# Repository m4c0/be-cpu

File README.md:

# be-cpu

Before trying to dig in this project, please check out Ben Eater's [YouTube Playlist](https://www.youtube.com/watch?v=HyznrdDSSGM&list=PLowKtXNTBypGqImE405J2565dvjafglHU) first. That's an amazing material, and he deserves a lot of credits (and tips, as well).

This repository contains my own version of Ben Eater's CPU. Some people build cars in their spare time, I build a CPU. I'm open-sourcing it because Ben's design is open as well - and Open Source Hardware is a cool concept. Maybe there'll be some videos on my own in the future; maybe I'll sell kits... Only time will tell.

## Mission

Be fun. "Fun" is more important than "cool". The final result may be cool, but the path will definitely be fun. It's what [Arduino](https://www.arduino.cc) does in the microcontroller market - there are ICs faster than ATmega, with more memory, IOs and resources in general, but it's fun to work with Arduino and you can make cool stuff with it. 

## General design decisions

One noticeable difference from Ben's original design is the usage of SMD instead of THT. Mainly because I like designing and soldering using SMD (althought I'm still learning).

Also, due to pricing and availability, the 74LS chips are being replaced with their CMOS variants - mostly 74HC. It has a wide range of voltages, supporting from 2V up to 6V. 74HCT would be strictier, supporting 4.5 to 5V, which is right at the edge of what USB can provide. The 2-6V range allows us to change the supply voltage as required.

Ben also tried to split his design into modules, but not all modules had its own breadbord. The same goes here, but the design is strongly modular, with one module per "PCB card".

The clock is slow - this is not a design to run in the scale of MHz. It's meant to see what the CPU is doing as it runs simple algorithms, in a very low clock (less than 1kHz - TBC). This also allows the design to be "EMI-free" (as in "don't need to care about EMI"). 2-layer boards and lack of extra ground pins will be a thing here.

Note: being able to implement [RISC-V](https://riscv.org) would be interesting, but definitely unfeasible with those modules.

## Versions

*Note:* Due to time (and money) restrictions, some combination of version/modules may not be tested, yet.

### BE - Eater's version

This is as close as possible to Ben's own version. There's no substantial change in his design, other than changes that are required to make the CPU work, and current-limiting resistors.

Since Ben's design works, troubleshooting those modules will be easier. This version then acts as a "reference design" when experimenting new designs and ideas for other versions.

#### Clock

The version 0.1 follows these original design decisions (shown in [this video](https://www.youtube.com/watch?v=SmQ5K7UQPMM)):

* One astable 555 as a clock
* One monostable 555 as a push button debouncer
* One bistable 555 as a switch debouncer
* One 7404, one 7408 and one 7432 to apply the logic to get the result of the three 555s as a final clock
* One LED with the clock output
* The button and the switch to be debounced
* A trimpot to select the astable clock speed

I took the liberty of doing these changes:

* Add three pads with the outputs of the 555s. This way, we can see the results of the individual ICs with a voltimeter/oscilloscope or by soldering LEDs. This gives the same visual feedback as used by Ben until he finishes the module
* The final board has male pin headers for VCC/GND, CLK/HLT, and eight extras, to reserve space for the bus. This is an attempt to make a standard for the modules, in a way both bus and signals are handled by a transversal companion board (to be developed).
* Pins for the 74xx family were changed to allow a more compact design

The whole design currently fits in a 4x3.4cm board. You can buy one for yourself at [OSHPark](https://oshpark.com/shared_projects/r4cIYBAv).

Improvements for the next revision:

* Add a OSH stamp to the back silk
* Increase the LED resistor (currently at 220), because the LED is annoyingly bright now. It seems 470 gives a nice result, but testing showed it varies with the load at the CLK pin - powering another LED from CLK drastically reduces the onboard LED brightness. This may be the end result after all modules are tied up to the same CLK bus.
* Increase the push button debounce time (it works, but it feels faster than it should)
* Find more SMD-friendly button, switch and trimpot
* Flip the design. The pin header is on top, so all text is upside-down and it drives me nuts

#### Register

The version 0.1 of that module contain these from the original design (shown in [this video](https://www.youtube.com/watch?v=CiMaWbz_6E8)):

* Two 74173 (quad D-Flip Flop with tri-state output, async clear and chip-select) to read from the bus and store the value
* One 74245 (tri-state bi-directional buffer) to enable output the value to the bus on-demand
* Eight LEDs to show the output of the 74173 (effectively, the value of the register, even if not outputting to the bus)
* There are four signals: clock, reset (tied up to the MR of the 74173), output enabled (inverted), input enabled (inverted)

There's only one considerable change in this design. The output LEDs has current limiting resistors - currently 220ohms.

It also contains an extra 8-bit header from the output of the 74173. This serves for "hot linking" the register without the bus - in this case, "A" and "B" registers and the ALU input.

The whole design currently fits in a 4.5x3.2cm board. You can buy one for yourself at [OSHPark](https://oshpark.com/shared_projects/CUKuVAHy).

Improvements for the next revision:

* Add a OSH stamp to the back silk
* Consider a dual hot-link pin header, allowing to "sandwich" the ALU using standard headers
* Realign the hot-link to be easier to copy over to the ALU

#### ALU

The version 0.1 of that module contain these from the original design (shown in [Ben's site](https://eater.net/8bit/alu)):

* Two 74283 (4-bit ALU)
* Two 7486 (Quad-XOR) to conditionally invert input "B"
* One 74245 (tri-state bi-directional buffer) to enable output the value to the bus on-demand
* Eight LEDs to show the output of the 74283 (effectively, the output of the ALU, even if not outputting to the bus)
* One 7402 (Quad-NOR) and one 7408 (Quad-AND) to create the "zero flag" whenever the output of ALU is zero
* One 74173 (Quad D-FF) to act as a "flag register", storing the "zero flag" and the "carry flag"
* Two extra LEDs to show ZF and CF (unbuffered)

This board exposes a double-sided 16-bit header (8-bit each side) to hot-link A and B registers.

The whole design currently fits in a 5.7x3.8cm board.

#### RAM

Currently on research. Until said otherwise, this module won't have a "BE" version, since there's no 74189 in SMD. All major manufacturers discontinued that product, and the "unbranded" Chinese manufacturers only sells them in THT.

#### Bus

No board yet, only some ideas. This should contain pin headers for all modules. All signals will be hardcoded, to simplify the design of the individual modules.

### BM - My own version

This is my own version of Ben's CPU. It will replace components and change architecture. Since it's laxed, more experimental features goes here.

#### Clock

Still in planning. Current plan:

* One astable 555 as a clock
* A RC+Shimitt Trigger for debouncing the push button

Questions to answer:

* Is there a better way to debounce the toggle switch?
* What's the minimal circuit to do the logic (switch+halt)?

#### Register

Questions/ideas:

* Use a 74377 (Octal DFF), saving one IC
* Check if the 74377 can drive eight LEDs - maybe use a ULN2803 as LED driver
* Remove the reset input. A "global reset" may be achieveable if we keep the pull-down resistors on the bus and we enable all register's input - this way, the bus will be zeroed and the registers will latch that value.
* Can we send IE/OE already in sync with the clock?

#### ALU

#### RAM

#### Bus

Idea:

* Allow customization of the bus signal

### BC - Compact and cheap

This is will be smaller and containing less modules (or cheaper ones). All modules will be non-suitable for children under 4, because they will be tiny (1.35"/3.7cm wide). It provides building blocks to easily test high level architectures, while still being a good educational toy.

The main bus will probably be done with card edges connecting to a `HSEC8-120-01-SM-DV-A` from Samtec (or, at least, some 0.8mm similar product).

The connector will be partially reversible. When reversed, it will allow the board to operate on a different bus. One side will be the "main bus" and the other will be the "secondary bus".

#### Register

This is a 17.2x35mm board with a 74377 (Octal DFF), a 74245 (Bus Driver) and a ULN2803 (LED Driver). It supports a single bus, like Ben's original design. Also following his design, register "A" will be on main bus, and "B" will be secondary. Probably...

The absence of reset follows the same idea used in BM - the reset can be done by enabling the output and leaving the bus grounded.

Currently, this is not tested yet. The BM will be used as "test bench" for some ideas, like removing the ULN2803 or changing the flip-flop IC.

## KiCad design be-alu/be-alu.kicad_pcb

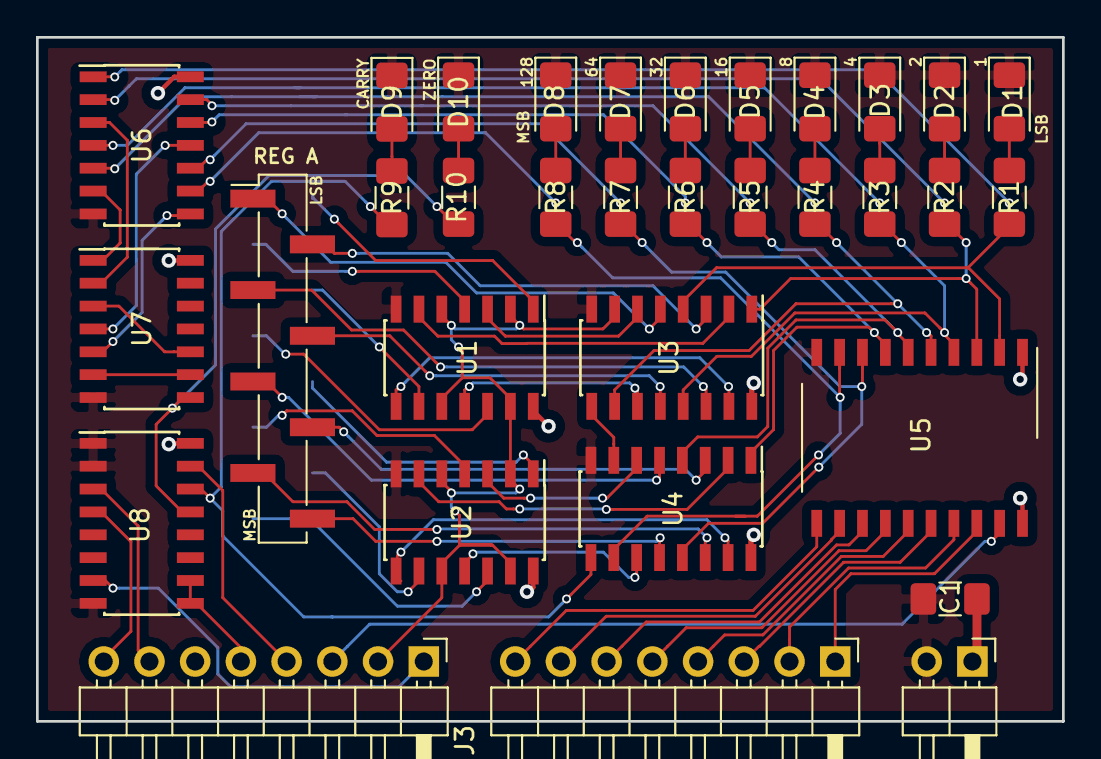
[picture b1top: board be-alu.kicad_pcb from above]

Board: 2 copper layers, 57.0 x 38.0 mm, 34 parts (1 on the bottom side), 68 nets.

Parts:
C1: 0.1u; C_1206_3216Metric_Pad1.42x1.75mm_HandSolder
D1, D2, D3, D4, D5, D6, D7, D8, D9, D10: LED; LED_1206_3216Metric_Pad1.42x1.75mm_HandSolder
J1: Conn_01x02; PinHeader_1x02_P2.54mm_Horizontal
J2, J3: Conn_01x08; PinHeader_1x08_P2.54mm_Horizontal
J4, J5: Conn_01x08; PinHeader_1x08_P2.54mm_Vertical_SMD_Pin1Left
R1, R2, R3, R4, R5, R6, R7, R8, R9, R10: 220; R_1206_3216Metric_Pad1.42x1.75mm_HandSolder
U1, U2: 74LS86; SOIC-14_3.9x8.7mm_P1.27mm
U3, U4: 74LS283; SOIC-16_3.9x9.9mm_P1.27mm
U5: 74LS245; SO-20_12.8x7.5mm_P1.27mm
U6: 7402; SOIC-14_3.9x8.7mm_P1.27mm
U7: 7408; SOIC-14_3.9x8.7mm_P1.27mm
U8: 74LS173; SOIC-16_3.9x9.9mm_P1.27mm

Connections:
/A0: J4.1, U3.5
/A1: J4.2, U3.3
/A2: J4.3, U3.14
/A3: J4.4, U3.12
/A4: J4.5, U4.5
/A5: J4.6, U4.3
/A6: J4.7, U4.14
/A7: J4.8, U4.12
/B0: J5.1, U1.1
/B1: J5.2, U1.4
/B2: J5.3, U1.9
/B3: J5.4, U1.12
/B4: J5.5, U2.1
/B5: J5.6, U2.4
/B6: J5.7, U2.9
/B7: J5.8, U2.12
/BUS0: J2.1, U5.18
/BUS1: J2.2, U5.17
/BUS2: J2.3, U5.16
/BUS3: J2.4, U5.15
/BUS4: J2.5, U5.14
/BUS5: J2.6, U5.13
/BUS6: J2.7, U5.12
/BUS7: J2.8, U5.11
/C4: U3.9, U4.7
/CF: J3.7, U8.3
/CLK: J3.1, U8.7
/RAW0: R1.2, U3.4, U5.2, U6.1
/RAW1: R2.2, U3.1, U5.3, U6.2
/RAW2: R3.2, U3.13, U5.4, U6.4
/RAW3: R4.2, U3.10, U5.5, U6.5
/RAW4: R5.2, U4.4, U5.6, U6.13
/RAW5: R6.2, U4.1, U5.7, U6.12
/RAW6: R7.2, U4.13, U5.8, U6.10
/RAW7: R8.2, U4.10, U5.9, U6.9
/RAW_CF: R9.2, U4.9, U8.14
/RAW_ZF: R10.2, U7.8, U8.13
/RST: J3.4, U8.15
/SU: J3.2, U1.2, U1.5, U1.10, U1.13, U2.2, U2.5, U2.10, U2.13, U3.7
/ZF: J3.8, U8.4
/~B0: U1.3, U3.6
/~B1: U1.6, U3.2
/~B2: U1.8, U3.15
/~B3: U1.11, U3.11
/~B4: U2.3, U4.6
/~B5: U2.6, U4.2
/~B6: U2.8, U4.15
/~B7: U2.11, U4.11
/~EO: J3.3, U5.19
/~FI: J3.5, U8.9, U8.10
GND: C1.2, D1.1, D2.1, D3.1, D4.1, D5.1, D6.1, D7.1, D8.1, D9.1, D10.1, J1.2, U1.7, U2.7, U3.8, U4.8, U5.10, U6.7, U7.7, U8.1, U8.2, U8.8
unnamed: D1.2, R1.1
unnamed: D2.2, R2.1
unnamed: D3.2, R3.1
unnamed: D4.2, R4.1
unnamed: D5.2, R5.1
unnamed: D6.2, R6.1
unnamed: D7.2, R7.1
unnamed: D8.2, R8.1
unnamed: D9.2, R9.1
unnamed: D10.2, R10.1
unnamed: U6.3, U7.2
unnamed: U6.6, U7.1
unnamed: U6.8, U7.5
unnamed: U6.11, U7.4
unnamed: U7.6, U7.9
unnamed: U7.3, U7.10
VCC: C1.1, J1.1, U1.14, U2.14, U3.16, U4.16, U5.1, U5.20, U6.14, U7.14, U8.16

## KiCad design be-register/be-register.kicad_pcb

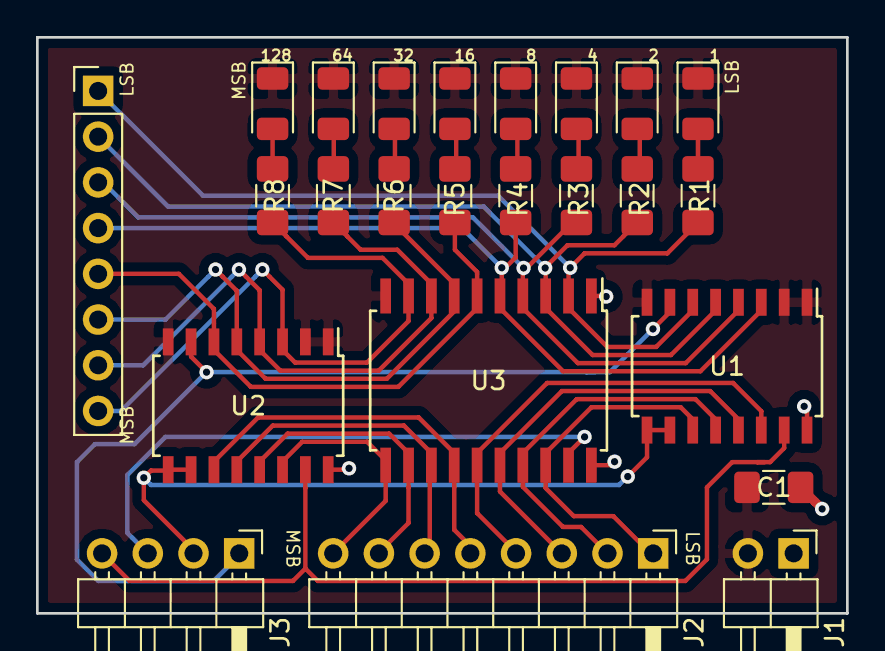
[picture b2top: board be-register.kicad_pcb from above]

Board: 2 copper layers, 45.0 x 32.0 mm, 24 parts (0 on the bottom side), 30 nets.

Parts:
C1: 0.01u; C_1206_3216Metric_Pad1.42x1.75mm_HandSolder
D1, D2, D3, D4, D5, D6, D7, D8: LED; LED_1206_3216Metric
J1: Conn_01x02; PinHeader_1x02_P2.54mm_Horizontal
J2: Conn_01x08; PinHeader_1x08_P2.54mm_Horizontal
J3: Conn_01x04; PinHeader_1x04_P2.54mm_Horizontal
J4: Conn_01x08; PinHeader_1x08_P2.54mm_Vertical
R1, R2, R3, R4, R5, R6, R7, R8: R; R_1206_3216Metric_Pad1.42x1.75mm_HandSolder
U1, U2: 74LS173; SOIC-16W_5.3x10.2mm_P1.27mm
U3: 74LS245; SOIC-20W_7.5x12.8mm_P1.27mm

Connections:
/BUS0: J2.1, U1.11, U3.18
/BUS1: J2.2, U1.12, U3.17
/BUS2: J2.3, U1.13, U3.16
/BUS3: J2.4, U1.14, U3.15
/BUS4: J2.5, U2.11, U3.14
/BUS5: J2.6, U2.12, U3.13
/BUS6: J2.7, U2.13, U3.12
/BUS7: J2.8, U2.14, U3.11
/CLK: J3.1, U1.7, U2.7
/RAW0: J4.1, R1.2, U1.6, U3.2
/RAW1: J4.2, R2.2, U1.5, U3.3
/RAW2: J4.3, R3.2, U1.4, U3.4
/RAW3: J4.4, R4.2, U1.3, U3.5
/RAW4: J4.5, R5.2, U2.6, U3.6
/RAW5: J4.6, R6.2, U2.5, U3.7
/RAW6: J4.7, R7.2, U2.4, U3.8
/RAW7: J4.8, R8.2, U2.3, U3.9
/RST: J3.4, U1.15, U2.15
/~IE: J3.2, U1.9, U1.10, U2.9, U2.10
/~OE: J3.3, U3.19
GND: C1.2, D1.1, D2.1, D3.1, D4.1, D5.1, D6.1, D7.1, D8.1, J1.2, U1.1, U1.2, U1.8, U2.1, U2.2, U2.8, U3.10
unnamed: D1.2, R1.1
unnamed: D2.2, R2.1
unnamed: D3.2, R3.1
unnamed: D4.2, R4.1
unnamed: D5.2, R5.1
unnamed: D6.2, R6.1
unnamed: D7.2, R7.1
unnamed: D8.2, R8.1
VCC: C1.1, J1.1, U1.16, U2.16, U3.1, U3.20

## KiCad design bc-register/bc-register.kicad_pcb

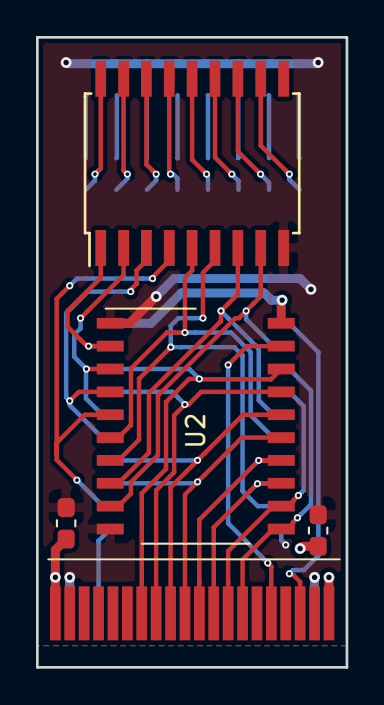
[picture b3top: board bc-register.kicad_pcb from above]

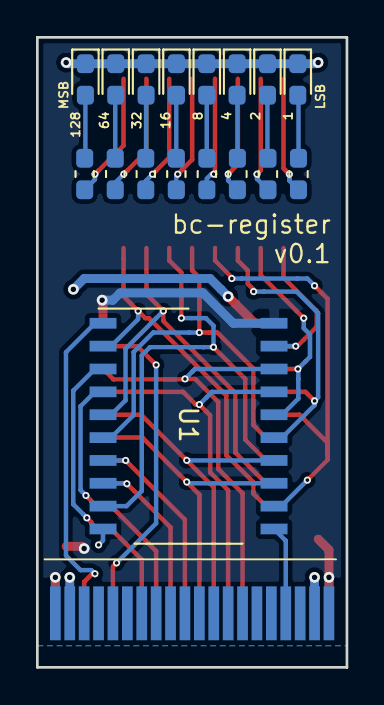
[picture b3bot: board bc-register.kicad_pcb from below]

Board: 2 copper layers, 17.2 x 35.0 mm, 22 parts (17 on the bottom side), 37 nets.

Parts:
C1, C2: 10u; C_0603_1608Metric_Pad1.05x0.95mm_HandSolder
D1, D2, D3, D4, D5, D6, D7, D8: LED; LED_0603_1608Metric_Pad1.05x0.95mm_HandSolder
J1: Conn_02x20_Odd_Even; card-edge-2x20-800um
R1, R2, R3, R4, R5, R6, R7, R8: R; R_0603_1608Metric_Pad1.05x0.95mm_HandSolder
U1: 74LS377; SO-20_12.8x7.5mm_P1.27mm
U2: 74LS245; SO-20_12.8x7.5mm_P1.27mm
U3: ULN2803A; SOIC-18W_7.5x11.6mm_P1.27mm

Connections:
/BUS0: J1.13, U1.18, U2.18
/BUS1: J1.15, U1.17, U2.17
/BUS2: J1.17, U1.14, U2.16
/BUS3: J1.19, U1.13, U2.15
/BUS4: J1.21, U1.7, U2.14
/BUS5: J1.23, U1.8, U2.13
/BUS6: J1.25, U1.4, U2.12
/BUS7: J1.27, U1.3, U2.11
/CLK: J1.8, J1.33, U1.11
/LED0: R1.2, U3.18
/LED1: R2.2, U3.17
/LED2: R3.2, U3.16
/LED3: R4.2, U3.15
/LED4: R5.2, U3.14
/LED5: R6.2, U3.13
/LED6: R7.2, U3.12
/LED7: R8.2, U3.11
/RAW0: U1.19, U2.2, U3.1
/RAW1: U1.16, U2.3, U3.2
/RAW2: U1.15, U2.4, U3.3
/RAW3: U1.12, U2.5, U3.4
/RAW4: U1.6, U2.6, U3.5
/RAW5: U1.9, U2.7, U3.6
/RAW6: U1.5, U2.8, U3.7
/RAW7: U1.2, U2.9, U3.8
/~IE: J1.35, U1.1
/~OE: J1.31, U2.19
GND: C1.2, C2.2, D1.1, D2.1, D3.1, D4.1, D5.1, D6.1, D7.1, D8.1, J1.3, J1.4, J1.37, J1.38, U1.10, U2.1, U2.10, U3.9
unnamed: D1.2, R1.1
unnamed: D2.2, R2.1
unnamed: D3.2, R3.1
unnamed: D4.2, R4.1
unnamed: D5.2, R5.1
unnamed: D6.2, R6.1
unnamed: D7.2, R7.1
unnamed: D8.2, R8.1
VCC: C1.1, C2.1, J1.1, J1.2, J1.39, J1.40, U1.20, U2.20

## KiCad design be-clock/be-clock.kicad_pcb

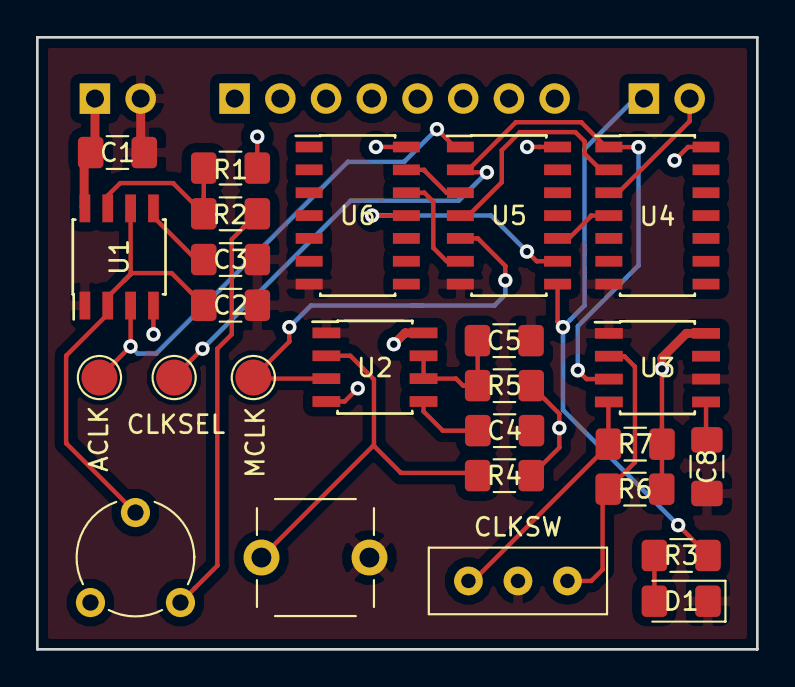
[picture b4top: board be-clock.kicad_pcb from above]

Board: 2 copper layers, 40.0 x 34.0 mm, 29 parts (0 on the bottom side), 23 nets.

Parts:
C1: 0.1u; C_1206_3216Metric_Pad1.42x1.75mm_HandSolder
C2, C5: 1u; C_1206_3216Metric_Pad1.42x1.75mm_HandSolder
C3, C4, C8: 0.01u; C_1206_3216Metric_Pad1.42x1.75mm_HandSolder
D1: LED; LED_1206_3216Metric_Pad1.42x1.75mm_HandSolder
J1: ACLK; TestPoint_Pad_D2.0mm
J2: MCLK; TestPoint_Pad_D2.0mm
J3: CLKSEL; TestPoint_Pad_D2.0mm
J4: Signals; PinHeader_1x02_P2.54mm_Horizontal
J5: Power; PinHeader_1x02_P2.54mm_Horizontal
J6: Bus; PinHeader_1x08_P2.54mm_Horizontal
R1, R2, R4, R5, R6, R7: 1k; R_1206_3216Metric_Pad1.42x1.75mm_HandSolder
R3: 330; R_1206_3216Metric_Pad1.42x1.75mm_HandSolder
RV1: 1M; Potentiometer_Piher_PT-6-V_Vertical
SW1: SW_Push; SW_PUSH_6mm
SW2: CLKSW; SW_DIP_SPSTx01_Slide_8.5x3.7mm
U1, U2, U3: NE555; SOIC-8_3.9x4.9mm_P1.27mm
U4: 74xx04; SOIC-14_3.9x8.7mm_P1.27mm
U5: 74xx08; SOIC-14_3.9x8.7mm_P1.27mm
U6: 74xx32; SOIC-14_3.9x8.7mm_P1.27mm

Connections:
/ACLK: J1.1, U1.3, U5.1
/CLK: J4.1, R3.2, U5.8
/CLKSEL: J3.1, U3.3, U4.1, U5.2
/CS_R: R7.1, SW2.1, U3.4
/CS_TR: R6.1, SW2.3, U3.2
/HLT: J4.2, U4.3
/MCLK: J2.1, U2.3, U5.5
GND: C1.1, C2.2, C3.2, C4.2, C5.1, C8.2, D1.1, J5.2, SW1.1, SW2.2, U1.1, U2.1, U3.1, U3.6, U4.7, U5.7, U6.7
unnamed: C2.1, RV1.2, U1.2, U1.6
unnamed: C3.1, U1.5
unnamed: C4.1, U2.5
unnamed: C5.2, R5.2, U2.6, U2.7
unnamed: C8.1, U3.5
unnamed: D1.2, R3.1
unnamed: R1.2, R2.2, U1.7
unnamed: R2.1, RV1.1
unnamed: R4.1, SW1.2, U2.2
unnamed: U4.2, U5.4
unnamed: U4.4, U5.10
unnamed: U5.3, U6.13
unnamed: U5.6, U6.12
unnamed: U5.9, U6.11
VCC: C1.2, J5.1, R1.1, R4.2, R5.1, R6.2, R7.2, U1.4, U1.8, U2.4, U2.8, U3.8, U4.14, U5.14, U6.14

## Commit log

2018-08-02 added a description of the clock module
2018-08-02 clock module v0.1
2018-08-09 typos in README
2018-08-16 basics of the register module
2018-08-16 laying out and wiring up the register module
2018-08-16 labeling pins and rotating 180, to make all ICs look correct
2018-08-17 added some notes about future designs
2018-08-21 trying out a compact, card-edge register module
2018-08-24 trying out more things in bc-register
2018-08-26 added decoupling caps and a lot of routing (plus OSHPark design rules)
2018-08-29 first version of the be-register module
2018-08-29 some docs about the future
2018-08-29 updating be-register docs after ordering some from oshpark
2018-08-30 Fixing units in the README
2018-09-03 improving README
2018-09-15 first sketch for the be-alu
2018-09-16 labels and other tweaks on be-alu
2018-09-16 updating README
2018-09-17 merging be-clock 74xx components into the 'global' library
2018-09-17 fixing path for be-alu's sym-lib-table
2018-09-18 finishing up the first version of be-alu (probably can be ordered as-is after the first batch of be-register is made)
